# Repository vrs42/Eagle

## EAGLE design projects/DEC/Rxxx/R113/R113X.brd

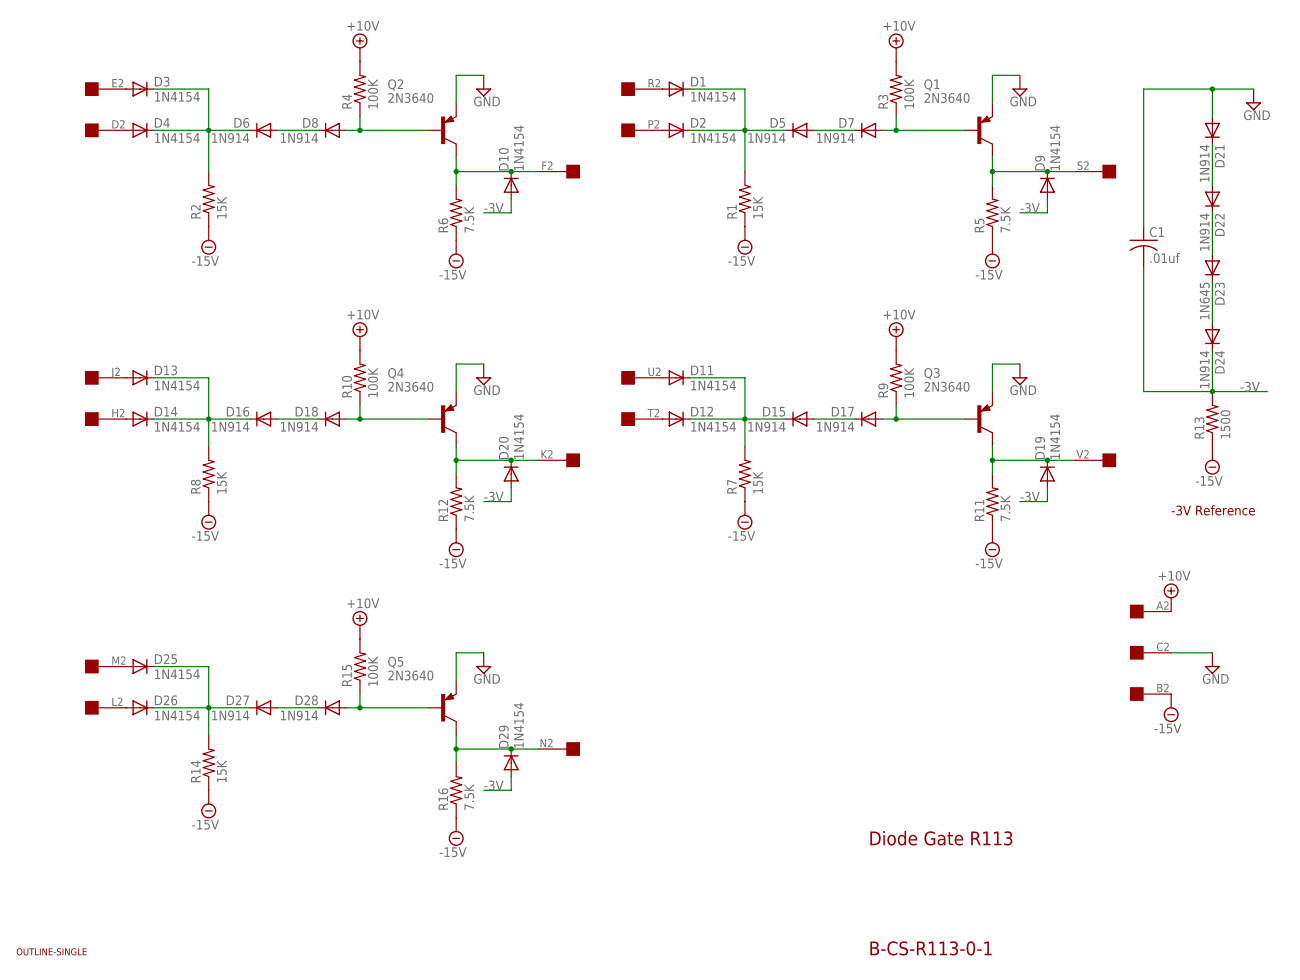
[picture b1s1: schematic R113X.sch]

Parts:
C1: .01uf; C050-025X075
D1, D2, D3, D4, D9, D10, D11, D12, D13, D14, D19, D20, D25, D26, D29: 1N4154; DO35-10
D5, D6, D7, D8, D15, D16, D17, D18, D21, D22, D24, D27, D28: 1N914; DO35-10
D23: 1N645; DO35-10
Q1, Q2, Q3, Q4, Q5: 2N3640; TO39
R1, R2, R7, R8, R14: 15K; 0207/10
R3, R4, R9, R10, R15: 100K; 0207/10
R5, R6, R11, R12, R16: 7.5K; 0207/10
R13: 1500; 0207/10
U$1: OUTLINE-SINGLE; SINGLE
U$2: EDGE-1; EDGE-CON1

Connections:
+10V: R3.2, R4.2, R9.2, R10.2, R15.2, U$2.A2
-3V: C1.2, D9.A, D10.A, D19.A, D20.A, D24.C, D29.A, R13.2
-15V: R1.1, R2.1, R5.1, R6.1, R7.1, R8.1, R11.1, R12.1, R13.1, R14.1, R16.1, U$2.B2
GND: C1.1, D21.A, Q1.1 (E), Q2.1 (E), Q3.1 (E), Q4.1 (E), Q5.1 (E), U$2.C2
unnamed: D14.A, U$2.H2
unnamed: D18.A, Q4.2 (B), R10.1
unnamed: D21.C, D22.A
unnamed: D20.C, Q4.3 (C), R12.2, U$2.K2
unnamed: D11.A, U$2.U2
unnamed: D13.C, D14.C, D16.C, R8.2
unnamed: D16.A, D18.C
unnamed: D28.A, Q5.2 (B), R15.1
unnamed: D29.C, Q5.3 (C), R16.2, U$2.N2
unnamed: D26.A, U$2.L2
unnamed: D25.C, D26.C, D27.C, R14.2
unnamed: D27.A, D28.C
unnamed: D22.C, D23.A
unnamed: D13.A, U$2.J2
unnamed: D7.A, Q1.2 (B), R3.1
unnamed: D23.C, D24.A
unnamed: D9.C, Q1.3 (C), R5.2, U$2.S2
unnamed: D2.A, U$2.P2
unnamed: D8.A, Q2.2 (B), R4.1
unnamed: D10.C, Q2.3 (C), R6.2, U$2.F2
unnamed: D4.A, U$2.D2
unnamed: D3.C, D4.C, D6.C, R2.2
unnamed: D6.A, D8.C
unnamed: D1.C, D2.C, D5.C, R1.2
unnamed: D5.A, D7.C
unnamed: D17.A, Q3.2 (B), R9.1
unnamed: D11.C, D12.C, D15.C, R7.2
unnamed: D15.A, D17.C
unnamed: D1.A, U$2.R2
unnamed: D12.A, U$2.T2
unnamed: D25.A, U$2.M2
unnamed: D19.C, Q3.3 (C), R11.2, U$2.V2
unnamed: D3.A, U$2.E2

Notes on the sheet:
Diode Gate R113
B-CS-R113-0-1
-3V Reference

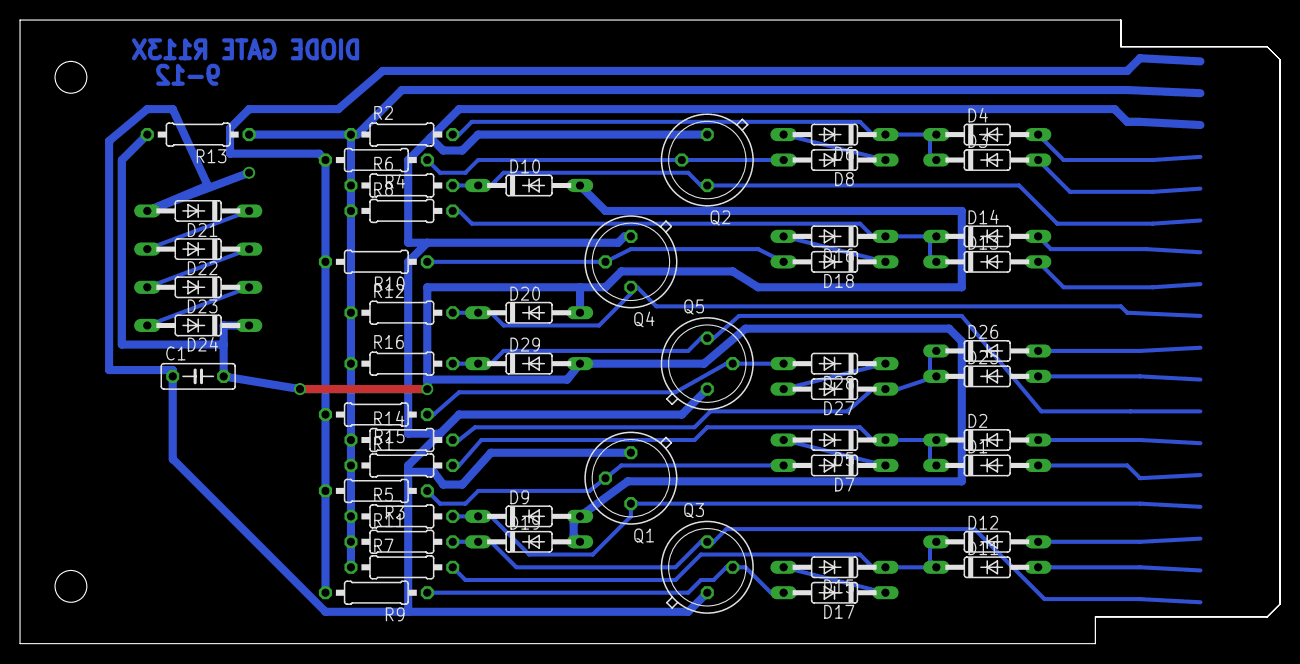
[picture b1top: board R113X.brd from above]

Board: 2 copper layers, 125.7 x 62.2 mm, 53 parts (0 on the bottom side), 37 nets.

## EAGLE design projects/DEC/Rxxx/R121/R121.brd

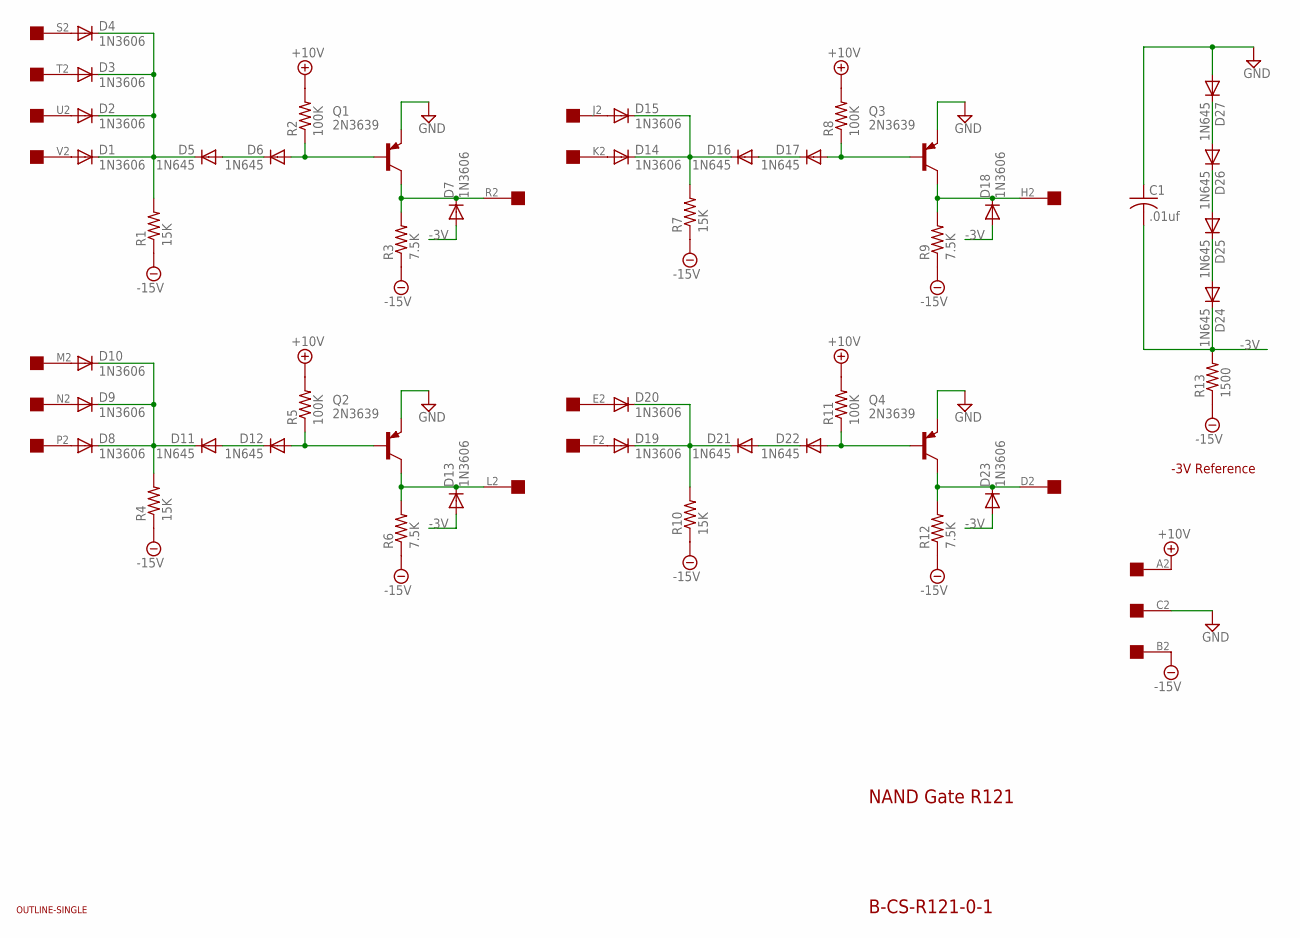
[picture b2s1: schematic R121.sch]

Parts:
C1: .01uf; C050-025X075
D1, D2, D3, D4, D7, D8, D9, D10, D13, D14, D15, D18, D19, D20, D23: 1N3606; DO35-10
D5, D6, D11, D12, D16, D17, D21, D22, D24, D25, D26, D27: 1N645; DO35-10
Q1, Q2, Q3, Q4: 2N3639; TO39
R1, R4, R7, R10: 15K; 0207/10
R2, R5, R8, R11: 100K; 0207/10
R3, R6, R9, R12: 7.5K; 0207/10
R13: 1500; 0207/10
U$1: OUTLINE-SINGLE; SINGLE
U$2: EDGE-1; EDGE-CON1

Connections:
+10V: R2.2, R5.2, R8.2, R11.2, U$2.A2
-3V: C1.2, D7.A, D13.A, D18.A, D23.A, D24.C, R13.2
-15V: R1.1, R3.1, R4.1, R6.1, R7.1, R9.1, R10.1, R12.1, R13.1, U$2.B2
GND: C1.1, D27.A, Q1.1 (E), Q2.1 (E), Q3.1 (E), Q4.1 (E), U$2.C2
unnamed: D8.A, U$2.P2
unnamed: D12.A, Q2.2 (B), R5.1
unnamed: D26.A, D27.C
unnamed: D13.C, Q2.3 (C), R6.2, U$2.L2
unnamed: D7.C, Q1.3 (C), R3.2, U$2.R2
unnamed: D8.C, D9.C, D10.C, D11.C, R4.2
unnamed: D11.A, D12.C
unnamed: D17.A, Q3.2 (B), R8.1
unnamed: D18.C, Q3.3 (C), R9.2, U$2.H2
unnamed: D14.A, U$2.K2
unnamed: D14.C, D15.C, D16.C, R7.2
unnamed: D16.A, D17.C
unnamed: D25.A, D26.C
unnamed: D9.A, U$2.N2
unnamed: D20.A, U$2.E2
unnamed: D24.A, D25.C
unnamed: D19.A, U$2.F2
unnamed: D22.A, Q4.2 (B), R11.1
unnamed: D6.A, Q1.2 (B), R2.1
unnamed: D4.A, U$2.S2
unnamed: D1.A, U$2.V2
unnamed: D1.C, D2.C, D3.C, D4.C, D5.C, R1.2
unnamed: D5.A, D6.C
unnamed: D23.C, Q4.3 (C), R12.2, U$2.D2
unnamed: D3.A, U$2.T2
unnamed: D19.C, D20.C, D21.C, R10.2
unnamed: D21.A, D22.C
unnamed: D10.A, U$2.M2
unnamed: D15.A, U$2.J2
unnamed: D2.A, U$2.U2

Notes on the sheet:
NAND Gate R121
B-CS-R121-0-1
-3V Reference

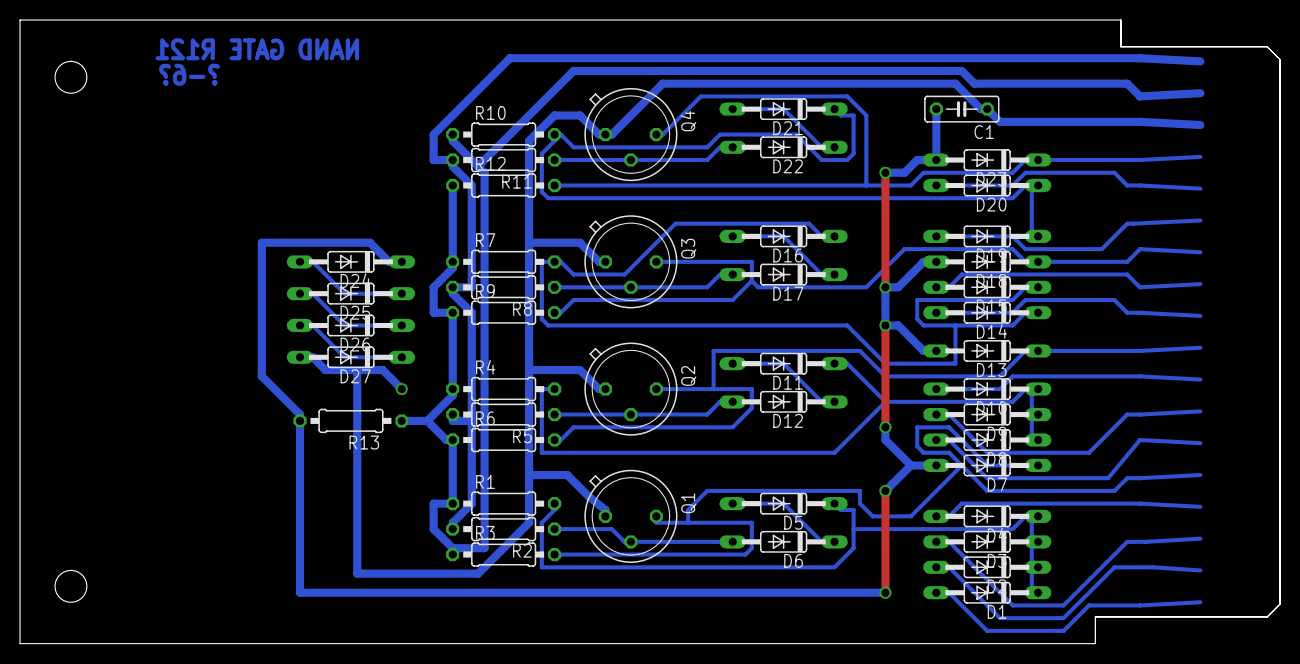
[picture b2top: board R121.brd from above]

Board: 2 copper layers, 125.7 x 62.2 mm, 47 parts (0 on the bottom side), 34 nets.

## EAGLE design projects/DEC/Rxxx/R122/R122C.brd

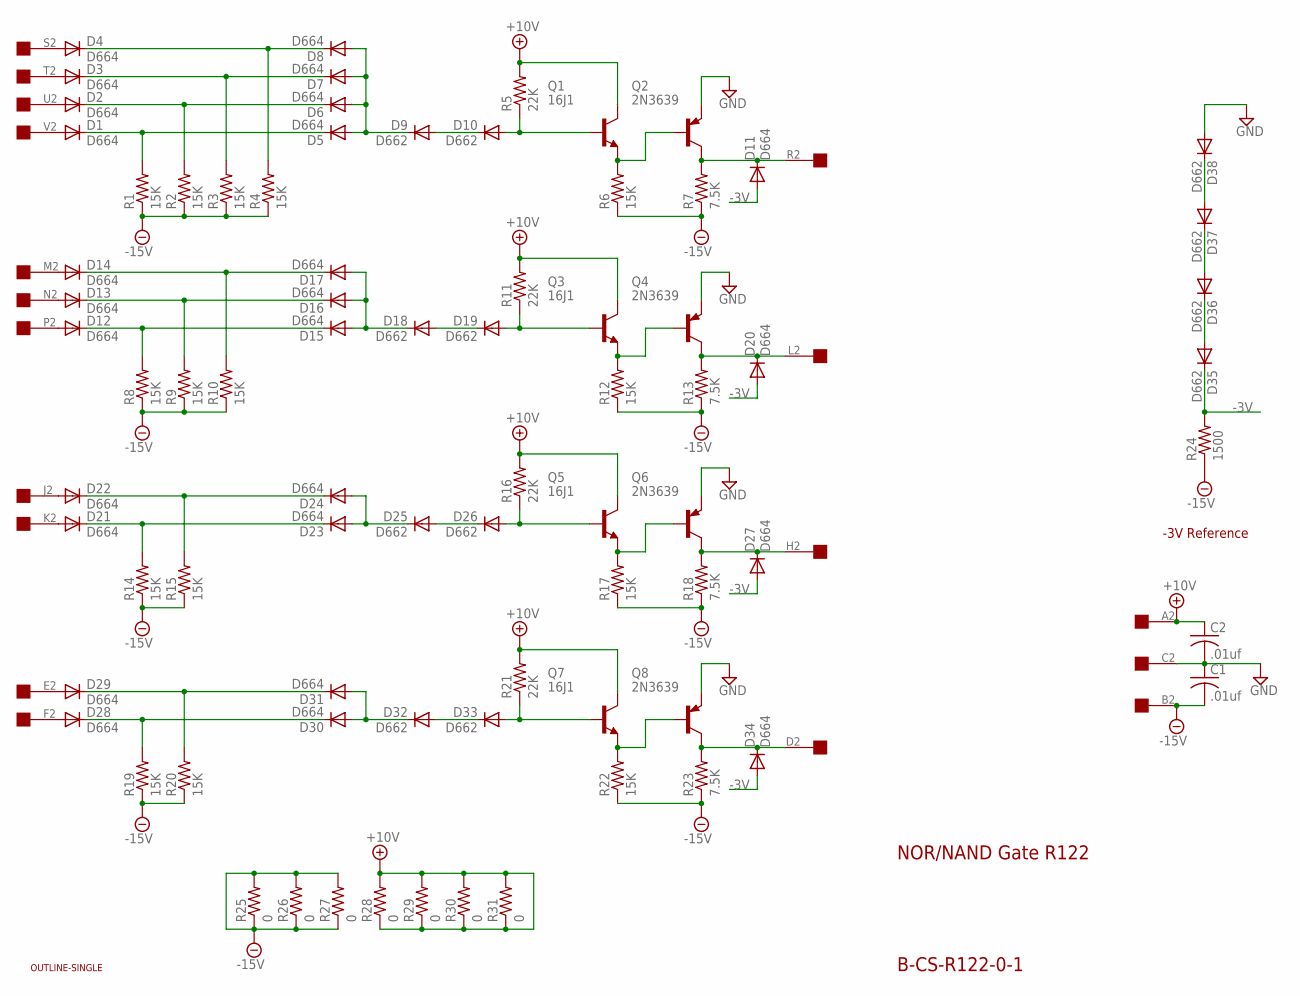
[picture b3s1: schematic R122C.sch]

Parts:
C1, C2: .01uf; C063-025X075
D1, D2, D3, D4, D5, D6, D7, D8, D11, D12, D13, D14, D15, D16, D17, D20, D21, D22, D23, D24, D27, D28, D29, D30, D31, D34: D664; DO35-10
D9, D10, D18, D19, D25, D26, D32, D33, D35, D36, D37, D38: D662; DO35-10
Q1, Q3, Q5, Q7: 16J1; TO39
Q2, Q4, Q6, Q8: 2N3639; TO39
R1, R2, R3, R4, R6, R8, R9, R10, R12, R14, R15, R17, R19, R20, R22: 15K; 0207/10
R5, R11, R16, R21: 22K; 0207/10
R7, R13, R18, R23: 7.5K; 0207/10
R24: 1500; 0207/10
R25, R26, R27, R28, R29, R30, R31: 0; 0207/10
U$1: OUTLINE-SINGLE; SINGLE
U$2: EDGE-1; EDGE-CON1

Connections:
+10V: C2.1, Q1.3 (C), Q3.3 (C), Q5.3 (C), Q7.3 (C), R5.2, R11.2, R16.2, R21.2, R28.1, R28.2, R29.1, R29.2, R30.1, R30.2, R31.1, R31.2, U$2.A2
-3V: D11.A, D20.A, D27.A, D34.A, D35.C, R24.2
-15V: C1.2, R1.1, R2.1, R3.1, R4.1, R6.1, R7.1, R8.1, R9.1, R10.1, R12.1, R13.1, R14.1, R15.1, R17.1, R18.1, R19.1, R20.1, R22.1, R23.1, R24.1, R25.1, R25.2, R26.1, R26.2, R27.1, R27.2, U$2.B2
GND: C1.1, C2.2, D38.A, Q2.1 (E), Q4.1 (E), Q6.1 (E), Q8.1 (E), U$2.C2
unnamed: D19.A, Q3.2 (B), R11.1
unnamed: D14.A, U$2.M2
unnamed: D37.A, D38.C
unnamed: D12.C, D15.C, R8.2
unnamed: D11.C, Q2.3 (C), R7.2, U$2.R2
unnamed: D18.A, D19.C
unnamed: D13.A, U$2.N2
unnamed: D20.C, Q4.3 (C), R13.2, U$2.L2
unnamed: D12.A, U$2.P2
unnamed: D21.A, U$2.K2
unnamed: D15.A, D16.A, D17.A, D18.C
unnamed: D22.A, U$2.J2
unnamed: D36.A, D37.C
unnamed: D14.C, D17.C, R10.2
unnamed: D13.C, D16.C, R9.2
unnamed: D35.A, D36.C
unnamed: Q3.1 (E), Q4.2 (B), R12.2
unnamed: D26.A, Q5.2 (B), R16.1
unnamed: D10.A, Q1.2 (B), R5.1
unnamed: D4.A, U$2.S2
unnamed: D1.A, U$2.V2
unnamed: D1.C, D5.C, R1.2
unnamed: D9.A, D10.C
unnamed: D28.A, U$2.F2
unnamed: D3.A, U$2.T2
unnamed: D21.C, D23.C, R14.2
unnamed: D25.A, D26.C
unnamed: D29.A, U$2.E2
unnamed: D5.A, D6.A, D7.A, D8.A, D9.C
unnamed: D4.C, D8.C, R4.2
unnamed: D27.C, Q6.3 (C), R18.2, U$2.H2
unnamed: D3.C, D7.C, R3.2
unnamed: D2.C, D6.C, R2.2
unnamed: Q1.1 (E), Q2.2 (B), R6.2
unnamed: D23.A, D24.A, D25.C
unnamed: D2.A, U$2.U2
unnamed: D22.C, D24.C, R15.2
unnamed: Q5.1 (E), Q6.2 (B), R17.2
unnamed: D33.A, Q7.2 (B), R21.1
unnamed: D28.C, D30.C, R19.2
unnamed: D32.A, D33.C
unnamed: D34.C, Q8.3 (C), R23.2, U$2.D2
unnamed: D30.A, D31.A, D32.C
unnamed: D29.C, D31.C, R20.2
unnamed: Q7.1 (E), Q8.2 (B), R22.2

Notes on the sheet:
NOR/NAND Gate R122
B-CS-R122-0-1
-3V Reference

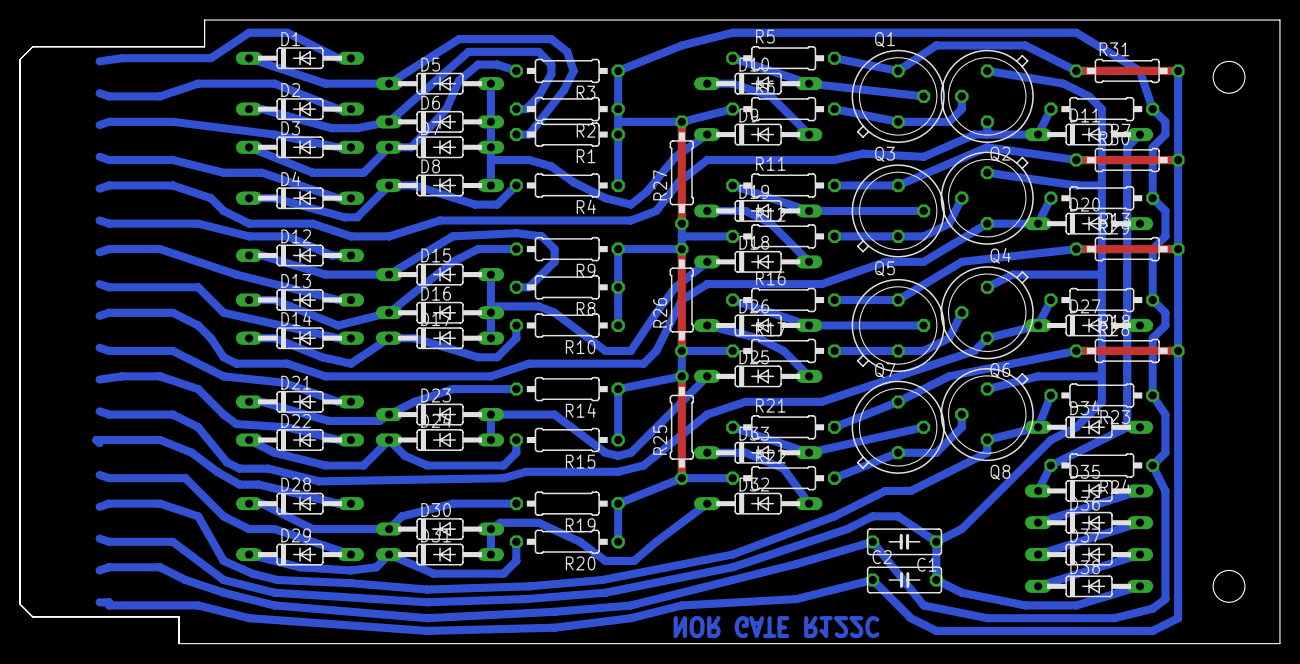
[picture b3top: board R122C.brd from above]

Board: 2 copper layers, 125.7 x 62.2 mm, 81 parts (0 on the bottom side), 49 nets.

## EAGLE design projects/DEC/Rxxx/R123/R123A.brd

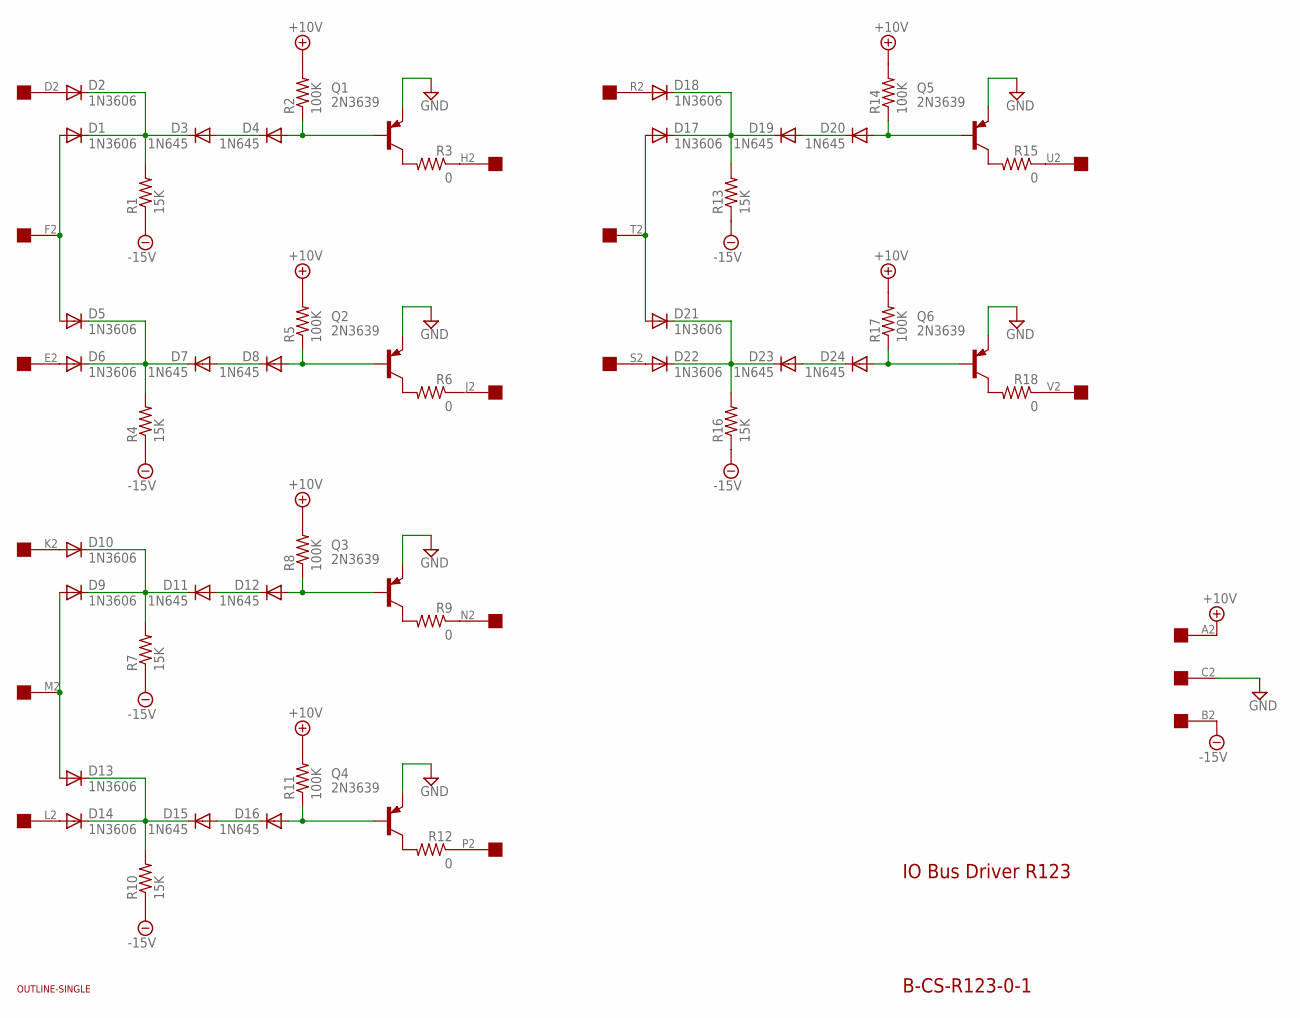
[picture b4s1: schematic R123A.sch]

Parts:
D1, D2, D5, D6, D9, D10, D13, D14, D17, D18, D21, D22: 1N3606; DO35-10
D3, D4, D7, D8, D11, D12, D15, D16, D19, D20, D23, D24: 1N645; DO35-10
Q1, Q2, Q3, Q4, Q5, Q6: 2N3639; TO39
R1, R4, R7, R10, R13, R16: 15K; 0207/10
R2, R5, R8, R11, R14, R17: 100K; 0207/10
R3, R6, R9, R12, R15, R18: 0; 0207/10
U$1: OUTLINE-SINGLE; SINGLE
U$2: EDGE-1; EDGE-CON1

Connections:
+10V: R2.2, R5.2, R8.2, R11.2, R14.2, R17.2, U$2.A2
-15V: R1.1, R4.1, R7.1, R10.1, R13.1, R16.1, U$2.B2
GND: Q1.1 (E), Q2.1 (E), Q3.1 (E), Q4.1 (E), Q5.1 (E), Q6.1 (E), U$2.C2
unnamed: D2.A, U$2.D2
unnamed: D8.A, Q2.2 (B), R5.1
unnamed: R3.1, U$2.H2
unnamed: Q2.3 (C), R6.2
unnamed: D6.A, U$2.E2
unnamed: D5.C, D6.C, D7.C, R4.2
unnamed: D7.A, D8.C
unnamed: D12.A, Q3.2 (B), R8.1
unnamed: Q3.3 (C), R9.2
unnamed: D9.A, D13.A, U$2.M2
unnamed: D9.C, D10.C, D11.C, R7.2
unnamed: D11.A, D12.C
unnamed: R6.1, U$2.J2
unnamed: D10.A, U$2.K2
unnamed: R9.1, U$2.N2
unnamed: R12.1, U$2.P2
unnamed: D18.A, U$2.R2
unnamed: R15.1, U$2.U2
unnamed: D4.A, Q1.2 (B), R2.1
unnamed: Q1.3 (C), R3.2
unnamed: D1.A, D5.A, U$2.F2
unnamed: D1.C, D2.C, D3.C, R1.2
unnamed: D3.A, D4.C
unnamed: D16.A, Q4.2 (B), R11.1
unnamed: Q4.3 (C), R12.2
unnamed: D14.A, U$2.L2
unnamed: D13.C, D14.C, D15.C, R10.2
unnamed: D15.A, D16.C
unnamed: D20.A, Q5.2 (B), R14.1
unnamed: Q5.3 (C), R15.2
unnamed: D17.A, D21.A, U$2.T2
unnamed: D17.C, D18.C, D19.C, R13.2
unnamed: D19.A, D20.C
unnamed: D24.A, Q6.2 (B), R17.1
unnamed: Q6.3 (C), R18.2
unnamed: D22.A, U$2.S2
unnamed: D21.C, D22.C, D23.C, R16.2
unnamed: D23.A, D24.C
unnamed: R18.1, U$2.V2

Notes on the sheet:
IO Bus Driver R123
B-CS-R123-0-1

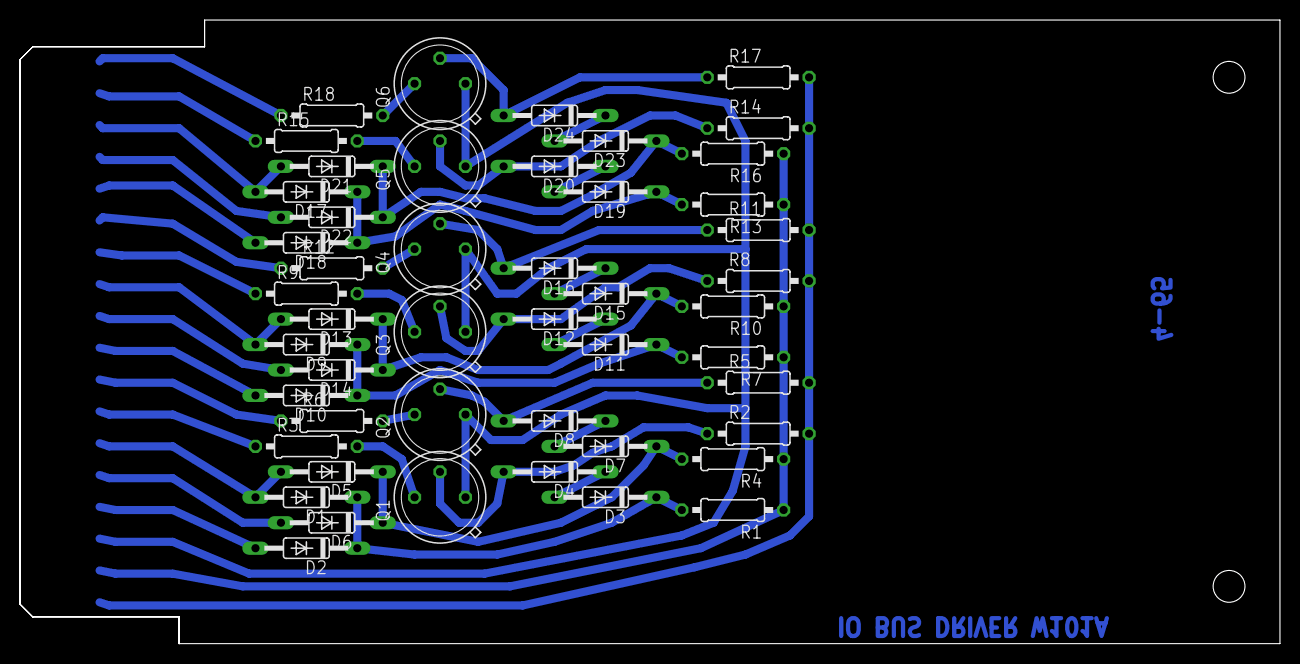
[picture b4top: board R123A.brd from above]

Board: 2 copper layers, 125.7 x 62.2 mm, 50 parts (0 on the bottom side), 42 nets.
